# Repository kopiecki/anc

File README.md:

# Active noise reduction system under the supervision of the Linux kernel with real-time extensions
The repository contains hardware, firmware and system software for master thesis project.

# Project structure
Project consists of a following modules:
- **base** - docker related stuff
- **hardware** - KiCAD electronics and PCB design
- **software** - application software environment
- **system** - system software, GNU/Linux OS building tools
- **docs** - school presentations and thesis draft

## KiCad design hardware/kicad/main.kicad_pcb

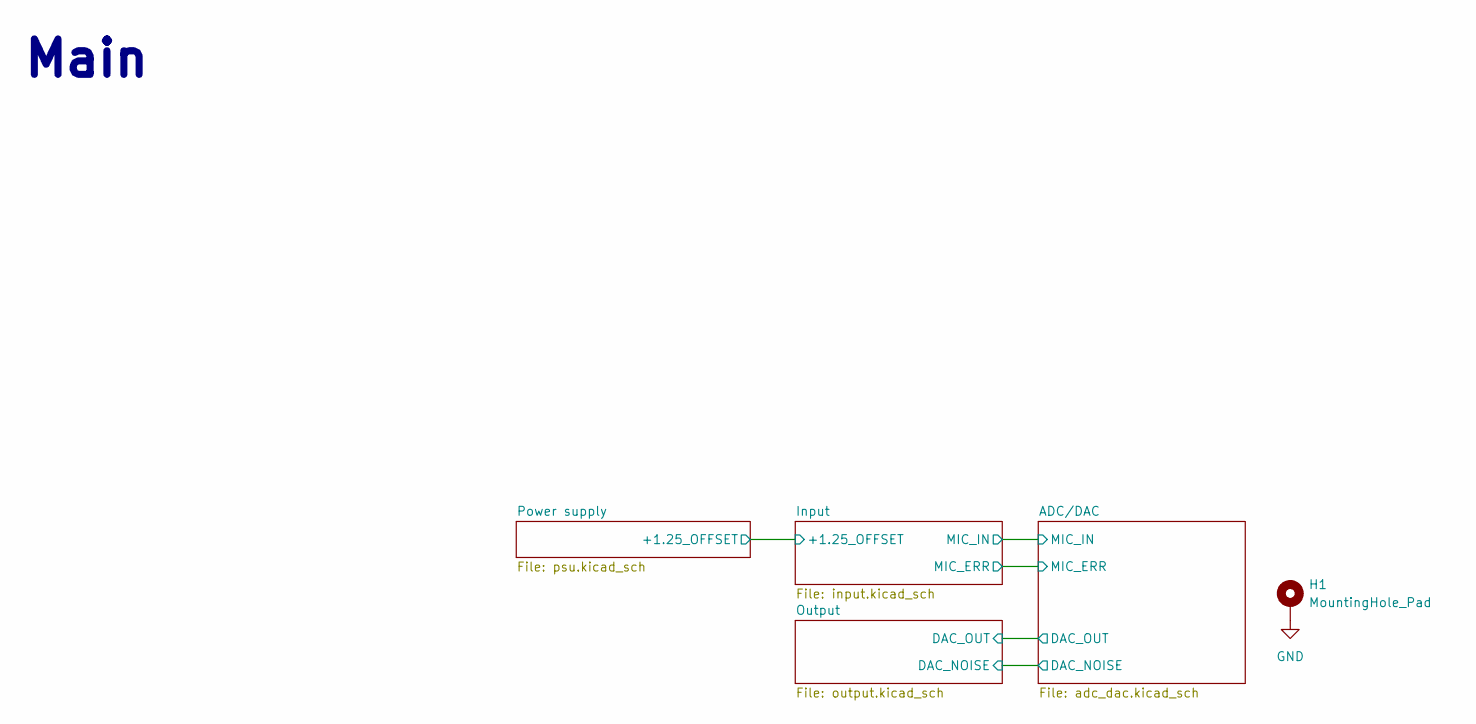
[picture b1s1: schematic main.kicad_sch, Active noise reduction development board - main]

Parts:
H1: MountingHole_Pad; MountingHole_2.7mm_Pad

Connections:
GND: H1.1; also elsewhere on the board

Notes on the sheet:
Main

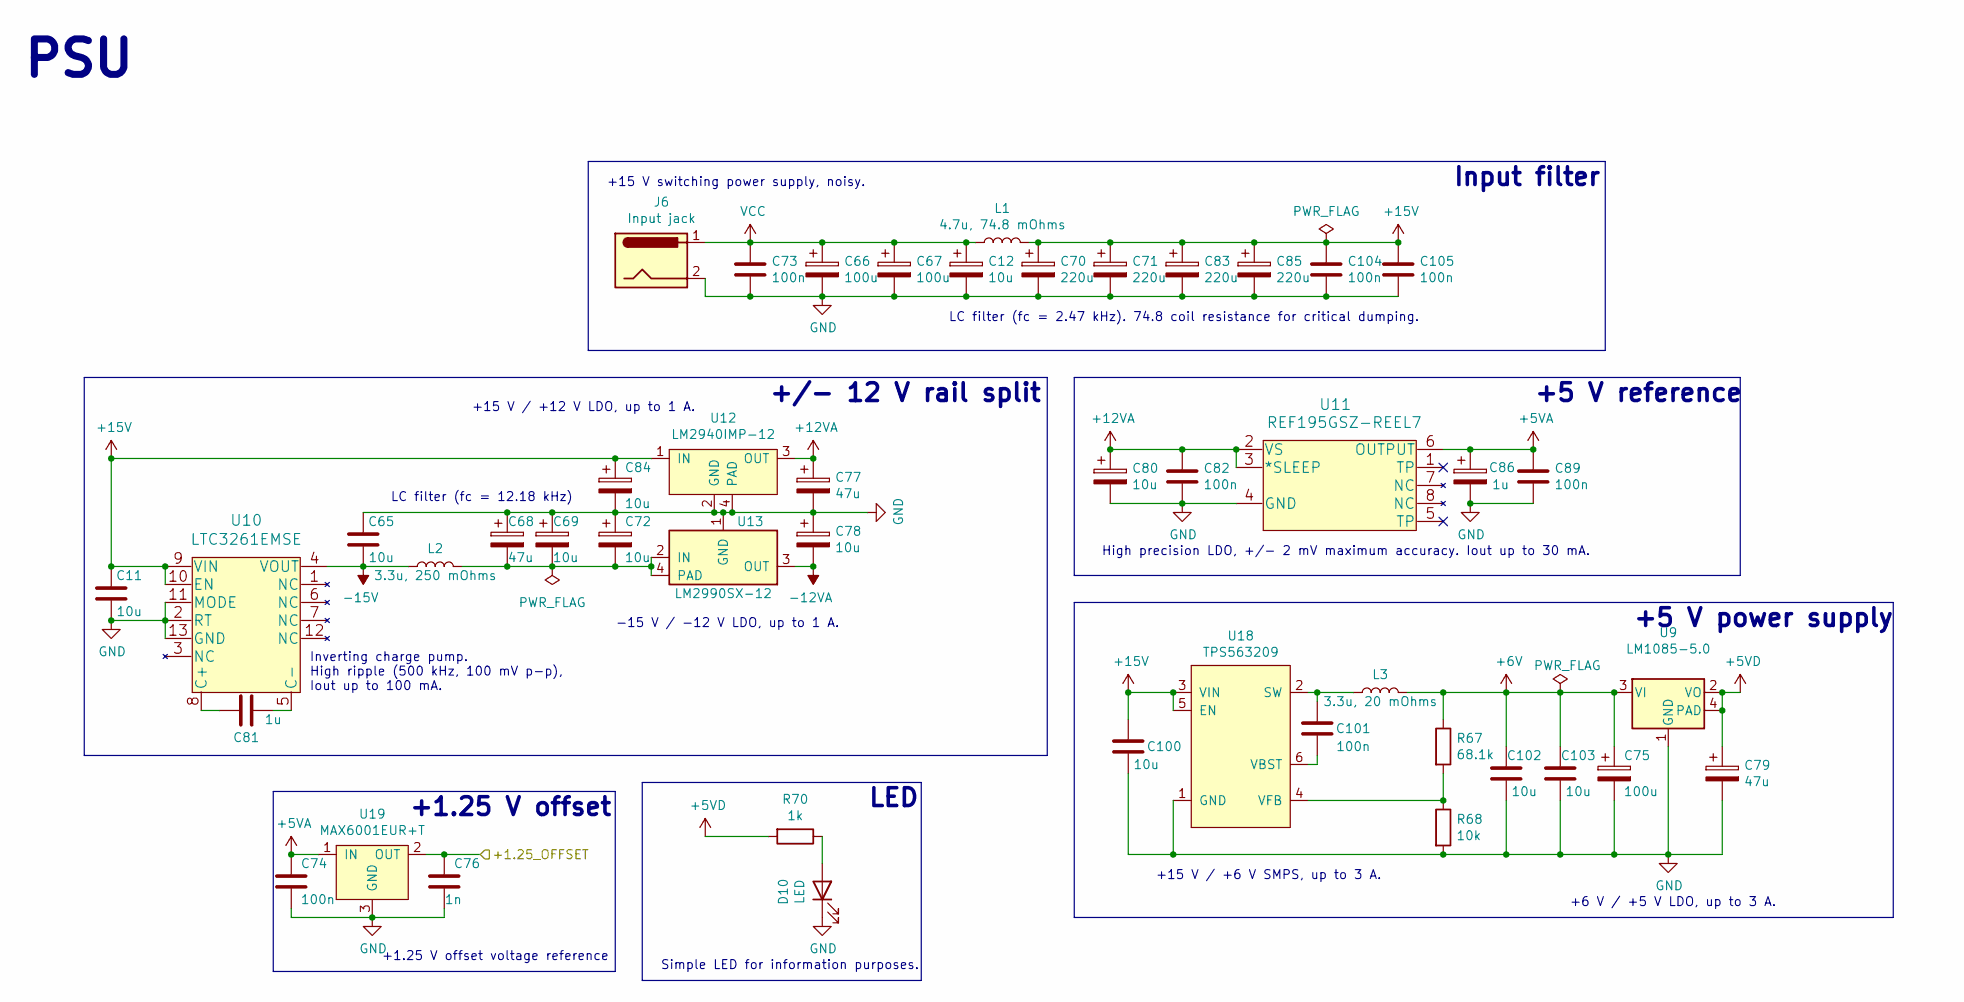
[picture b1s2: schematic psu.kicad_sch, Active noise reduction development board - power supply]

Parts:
C11, C65, C100, C102, C103: 10u; C_0805_2012Metric
C12, C69, C72, C78, C80, C84: 10u; CP_Elec_6.3x5.8
C66, C67, C75: 100u; CP_Elec_6.3x7.7
C68, C77, C79: 47u; CP_Elec_6.3x7.7
C70, C71, C83, C85: 220u; CP_Elec_10x10
C73, C74, C82, C89, C101, C104, C105: 100n; C_0603_1608Metric
C76: 1n; C_0603_1608Metric
C81: 1u; C_0603_1608Metric
C86: 1u; CP_Elec_4x5.4
D10: LED; LED_0603_1608Metric
J6: Input jack; BarrelJack_Horizontal
L1: 4.7u, 74.8 mOhms; L_Wuerth_MAPI-4020
L2: 3.3u, 250 mOhms; L_0805_2012Metric
L3: 3.3u, 20 mOhms; L_Wuerth_WE-PD2-Typ-L
R67: 68.1k; R_0805_2012Metric
R68: 10k; R_0805_2012Metric
R70: 1k; R_0603_1608Metric
U9: LM1085-5.0; LM1085IS-12&slash_NOPB
U10: LTC3261EMSE; ltc3261emse-pbf
U11: REF195GSZ-REEL7
U12: LM2940IMP-12; LM2940IMP-10&slash_NOPB
U13: LM2990SX-12; LM2990S-12
U18: TPS563209; TPS563209DDCR
U19: MAX6001EUR+T; SOT-23

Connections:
+5VA: C74.1, C86.1, C89.1, U11.6 (OUTPUT), U19.1 (IN); also elsewhere on the board
+5VD: C79.1, R70.2, U9.2 (VO), U9.4 (PAD); also elsewhere on the board
+6V: C75.1, C102.2, C103.2, L3.2, R67.1, U9.3 (VI)
+12VA: C77.1, C80.1, C82.1, U11.2 (VS), U11.3 (*SLEEP), U12.3 (OUT); also elsewhere on the board
+15V: C11.2, C70.1, C71.1, C83.1, C84.1, C85.1, C100.2, C104.1, C105.1, L1.2, U10.9 (VIN), U10.10 (EN), U12.1 (IN), U18.3 (VIN), U18.5 (EN)
-12VA: C78.2, U13.3 (OUT); also elsewhere on the board
-15V: C65.1, L2.1, U10.4 (VOUT)
/Input/+1.25_OFFSET: C76.1, U19.2 (OUT); also elsewhere on the board
GND: C11.1, C12.2, C65.2, C66.2, C67.2, C68.1, C69.1, C70.2, C71.2, C72.1, C73.2, C74.2, C75.2, C76.2, C77.2, C78.1, C79.2, C80.2, C82.2, C83.2, C84.2, C85.2, C86.2, C89.2, C100.1, C102.1, C103.1, C104.2, C105.2, D10.1 (K), J6.2, R68.2, U9.1 (GND), U10.2 (RT), U10.11 (MODE), U10.13 (GND), U11.4 (GND), U12.2 (GND), U12.4 (PAD), U13.1 (GND), U18.1 (GND), U19.3 (GND); also elsewhere on the board
unnamed: C68.2, C69.2, C72.2, L2.2, U13.2 (IN), U13.4 (PAD)
unnamed: C81.1, U10.8 (C+)
unnamed: C81.2, U10.5 (C-)
unnamed: C101.1, U18.6 (VBST)
unnamed: C101.2, L3.1, U18.2 (SW)
unnamed: D10.2 (A), R70.1
unnamed: R67.2, R68.1, U18.4 (VFB)
VCC: C12.1, C66.1, C67.1, C73.1, J6.1, L1.1

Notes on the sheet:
+15 V switching power supply, noisy.
LC filter (fc = 12.18 kHz)
PSU
LED
+15 V / +12 V LDO, up to 1 A.
Simple LED for information purposes.
-15 V / -12 V LDO, up to 1 A.
Inverting charge pump. High ripple (500 kHz, 100 mV p-p), Iout up to 100 mA.
Input filter
LC filter (fc = 2.47 kHz). 74.8 coil resistance for critical dumping.
+5 V power supply
+5 V reference
+6 V / +5 V LDO, up to 3 A.
+/- 12 V rail split
+15 V / +6 V SMPS, up to 3 A.
+1.25 V offset voltage reference
High precision LDO, +/- 2 mV maximum accuracy. Iout up to 30 mA.
+1.25 V offset

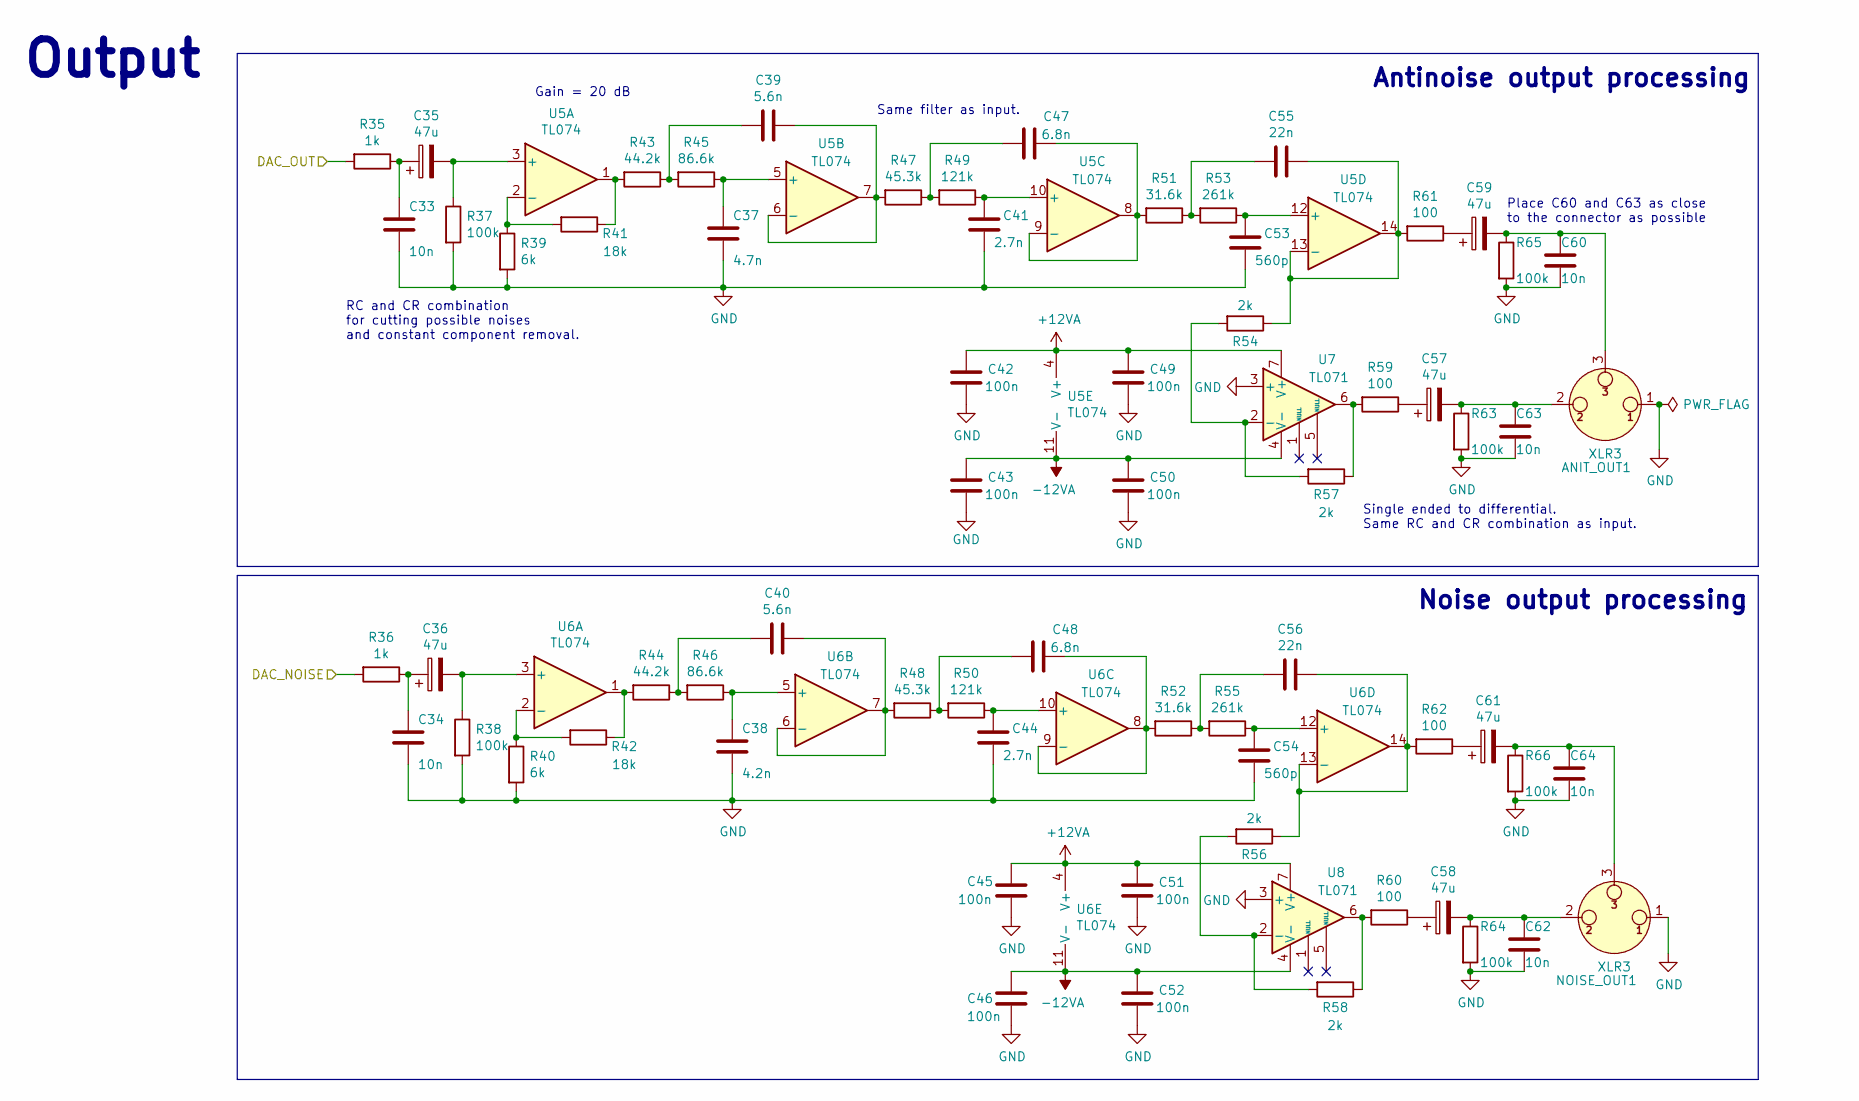
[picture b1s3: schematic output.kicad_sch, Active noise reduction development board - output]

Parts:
ANIT_OUT1: XLR3; Jack_XLR_Neutrik_NC3MAH-0_Horizontal
C33, C34, C60, C62, C63, C64: 10n; C_0603_1608Metric
C35, C36, C57, C58, C59, C61: 47u; CP_Elec_6.3x7.7
C37: 4.7n; C_0603_1608Metric
C38: 4.2n; C_0603_1608Metric
C39, C40: 5.6n; C_0603_1608Metric
C41, C44: 2.7n; C_0603_1608Metric
C42, C43, C45, C46, C49, C50, C51, C52: 100n; C_0603_1608Metric
C47, C48: 6.8n; C_0603_1608Metric
C53, C54: 560p; C_0603_1608Metric
C55, C56: 22n; C_0603_1608Metric
NOISE_OUT1: XLR3; Jack_XLR_Neutrik_NC3MAH-0_Horizontal
R35, R36: 1k; R_0603_1608Metric
R37, R38, R63, R64, R65, R66: 100k; R_0603_1608Metric
R39, R40: 6k; R_0603_1608Metric
R41, R42: 18k; R_0603_1608Metric
R43, R44: 44.2k; R_0603_1608Metric
R45, R46: 86.6k; R_0603_1608Metric
R47, R48: 45.3k; R_0603_1608Metric
R49, R50: 121k; R_0603_1608Metric
R51, R52: 31.6k; R_0603_1608Metric
R53, R55: 261k; R_0603_1608Metric
R54, R56, R57, R58: 2k; R_0603_1608Metric
R59, R60, R61, R62: 100; R_0603_1608Metric
U5, U6: TL074; TL074CD
U7, U8: TL071; TL071CD

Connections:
+12VA: C42.1, C45.1, C49.1, C51.1, U5.4 (V+), U6.4 (V+), U7.7 (V+), U8.7 (V+); also elsewhere on the board
-12VA: C43.1, C46.1, C50.1, C52.1, U5.11 (V-), U6.11 (V-), U7.4 (V-), U8.4 (V-); also elsewhere on the board
/ADC/DAC/DAC_NOISE: R36.2; also elsewhere on the board
/ADC/DAC/DAC_OUT: R35.2; also elsewhere on the board
GND: ANIT_OUT1.1, C33.2, C34.2, C37.2, C38.2, C41.2, C42.2, C43.2, C44.2, C45.2, C46.2, C49.2, C50.2, C51.2, C52.2, C53.2, C54.2, C60.2, C62.2, C63.2, C64.2, NOISE_OUT1.1, R37.2, R38.2, R39.2, R40.2, R63.2, R64.2, R65.2, R66.2, U7.3 (+), U8.3 (+); also elsewhere on the board
unnamed: ANIT_OUT1.2, C57.2, C63.1, R63.1
unnamed: ANIT_OUT1.3, C59.2, C60.1, R65.1
unnamed: C33.1, C35.1, R35.1
unnamed: C34.1, C36.1, R36.1
unnamed: C35.2, R37.1, U5.3 (+)
unnamed: C36.2, R38.1, U6.3 (+)
unnamed: C37.1, R45.1, U5.5 (+)
unnamed: C38.1, R46.1, U6.5 (+)
unnamed: C39.1, R43.1, R45.2
unnamed: C39.2, R47.2, U5.6 (-), U5.7
unnamed: C40.1, R44.1, R46.2
unnamed: C40.2, R48.2, U6.6 (-), U6.7
unnamed: C41.1, R49.1, U5.10 (+)
unnamed: C44.1, R50.1, U6.10 (+)
unnamed: C47.1, R47.1, R49.2
unnamed: C47.2, R51.2, U5.8, U5.9 (-)
unnamed: C48.1, R48.1, R50.2
unnamed: C48.2, R52.2, U6.8, U6.9 (-)
unnamed: C53.1, R53.1, U5.12 (+)
unnamed: C54.1, R55.1, U6.12 (+)
unnamed: C55.1, R51.1, R53.2
unnamed: C55.2, R54.1, R61.2, U5.13 (-), U5.14
unnamed: C56.1, R52.1, R55.2
unnamed: C56.2, R56.1, R62.2, U6.13 (-), U6.14
unnamed: C57.1, R59.1
unnamed: C58.1, R60.1
unnamed: C58.2, C62.1, NOISE_OUT1.2, R64.1
unnamed: C59.1, R61.1
unnamed: C61.1, R62.1
unnamed: C61.2, C64.1, NOISE_OUT1.3, R66.1
unnamed: R39.1, R41.2, U5.2 (-)
unnamed: R40.1, R42.2, U6.2 (-)
unnamed: R41.1, R43.2, U5.1
unnamed: R42.1, R44.2, U6.1
unnamed: R54.2, R57.2, U7.2 (-)
unnamed: R56.2, R58.2, U8.2 (-)
unnamed: R57.1, R59.2, U7.6
unnamed: R58.1, R60.2, U8.6

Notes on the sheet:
Place C60 and C63 as close to the connector as possible
Output
Gain = 20 dB
RC and CR combination for cutting possible noises and constant component removal.
Single ended to differential. Same RC and CR combination as input.
Noise output processing
Same filter as input.
Antinoise output processing

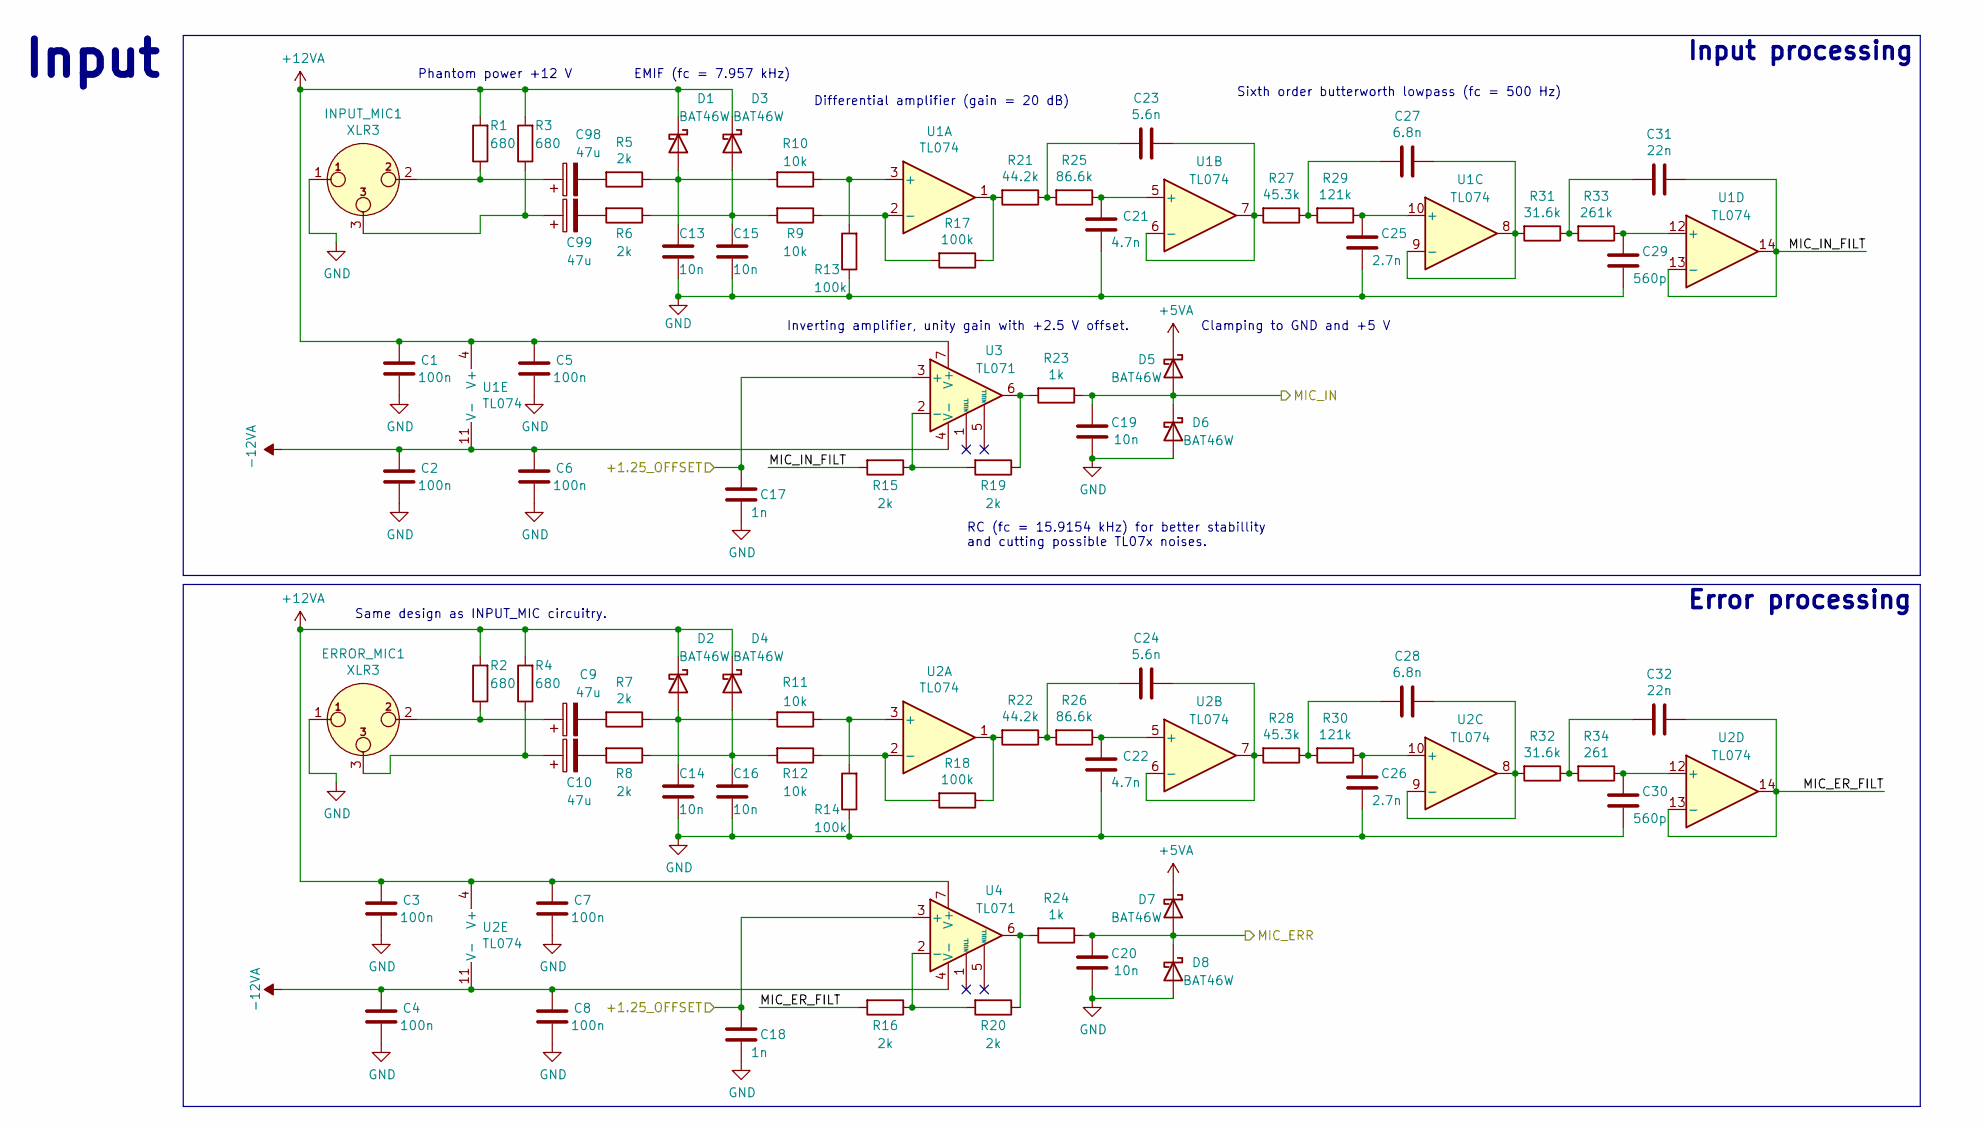
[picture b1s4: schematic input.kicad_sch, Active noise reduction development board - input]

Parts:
C1, C2, C3, C4, C5, C6, C7, C8: 100n; C_0603_1608Metric
C9, C10, C98, C99: 47u; CP_Elec_6.3x7.7
C13, C14, C15, C16, C19, C20: 10n; C_0603_1608Metric
C17, C18: 1n; C_0603_1608Metric
C21, C22: 4.7n; C_0603_1608Metric
C23, C24: 5.6n; C_0603_1608Metric
C25, C26: 2.7n; C_0603_1608Metric
C27, C28: 6.8n; C_0603_1608Metric
C29, C30: 560p; C_0603_1608Metric
C31, C32: 22n; C_0603_1608Metric
D1, D2, D3, D4, D5, D6, D7, D8: BAT46W; D_SOD-123F
ERROR_MIC1: XLR3; Jack_XLR_Neutrik_NC3MAH-0_Horizontal
INPUT_MIC1: XLR3; Jack_XLR_Neutrik_NC3MAH-0_Horizontal
R1, R2, R3, R4: 680; R_0805_2012Metric
R5, R6, R7, R8, R15, R16, R19, R20: 2k; R_0603_1608Metric
R9, R10, R11, R12: 10k; R_0603_1608Metric
R13, R14, R17, R18: 100k; R_0603_1608Metric
R21, R22: 44.2k; R_0603_1608Metric
R23, R24: 1k; R_0603_1608Metric
R25, R26: 86.6k; R_0603_1608Metric
R27, R28: 45.3k; R_0603_1608Metric
R29, R30: 121k; R_0603_1608Metric
R31, R32: 31.6k; R_0603_1608Metric
R33: 261k; R_0603_1608Metric
R34: 261; R_0603_1608Metric
U1, U2: TL074; TL074CD
U3, U4: TL071; TL071CD

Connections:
+5VA: D5.1 (K), D7.1 (K); also elsewhere on the board
+12VA: C1.1, C3.1, C5.1, C7.1, D1.1 (K), D2.1 (K), D3.1 (K), D4.1 (K), R1.2, R2.2, R3.2, R4.2, U1.4 (V+), U2.4 (V+), U3.7 (V+), U4.7 (V+); also elsewhere on the board
-12VA: C2.1, C4.1, C6.1, C8.1, U1.11 (V-), U2.11 (V-), U3.4 (V-), U4.4 (V-); also elsewhere on the board
/ADC/DAC/MIC_ERR: C20.1, D7.2 (A), D8.1 (K), R24.1; also elsewhere on the board
/ADC/DAC/MIC_IN: C19.1, D5.2 (A), D6.1 (K), R23.1; also elsewhere on the board
/Input/+1.25_OFFSET: C17.1, C18.1, U3.3 (+), U4.3 (+); also elsewhere on the board
/Input/MIC_ER_FILT: C32.2, R16.2, U2.13 (-), U2.14
/Input/MIC_IN_FILT: C31.2, R15.2, U1.13 (-), U1.14
GND: C1.2, C2.2, C3.2, C4.2, C5.2, C6.2, C7.2, C8.2, C13.2, C14.2, C15.2, C16.2, C17.2, C18.2, C19.2, C20.2, C21.2, C22.2, C25.2, C26.2, C29.2, C30.2, D6.2 (A), D8.2 (A), ERROR_MIC1.1, INPUT_MIC1.1, R13.1, R14.1; also elsewhere on the board
unnamed: C9.1, ERROR_MIC1.2, R2.1
unnamed: C9.2, R7.2
unnamed: C10.1, ERROR_MIC1.3, R4.1
unnamed: C10.2, R8.2
unnamed: C13.1, D1.2 (A), R5.1, R10.2
unnamed: C14.1, D2.2 (A), R7.1, R11.2
unnamed: C15.1, D3.2 (A), R6.1, R9.2
unnamed: C16.1, D4.2 (A), R8.1, R12.2
unnamed: C21.1, R25.1, U1.5 (+)
unnamed: C22.1, R26.1, U2.5 (+)
unnamed: C23.1, R21.1, R25.2
unnamed: C23.2, R27.2, U1.6 (-), U1.7
unnamed: C24.1, R22.1, R26.2
unnamed: C24.2, R28.2, U2.6 (-), U2.7
unnamed: C25.1, R29.1, U1.10 (+)
unnamed: C26.1, R30.1, U2.10 (+)
unnamed: C27.1, R27.1, R29.2
unnamed: C27.2, R31.2, U1.8, U1.9 (-)
unnamed: C28.1, R28.1, R30.2
unnamed: C28.2, R32.2, U2.8, U2.9 (-)
unnamed: C29.1, R33.1, U1.12 (+)
unnamed: C30.1, R34.1, U2.12 (+)
unnamed: C31.1, R31.1, R33.2
unnamed: C32.1, R32.1, R34.2
unnamed: C98.1, INPUT_MIC1.2, R1.1
unnamed: C98.2, R5.2
unnamed: C99.1, INPUT_MIC1.3, R3.1
unnamed: C99.2, R6.2
unnamed: R10.1, R13.2, U1.3 (+)
unnamed: R11.1, R14.2, U2.3 (+)
unnamed: R12.1, R18.2, U2.2 (-)
unnamed: R15.1, R19.2, U3.2 (-)
unnamed: R16.1, R20.2, U4.2 (-)
unnamed: R17.1, R21.2, U1.1
unnamed: R9.1, R17.2, U1.2 (-)
unnamed: R18.1, R22.2, U2.1
unnamed: R19.1, R23.2, U3.6
unnamed: R20.1, R24.2, U4.6

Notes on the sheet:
Phantom power +12 V
Same design as INPUT_MIC circuitry.
Differential amplifier (gain = 20 dB)
Sixth order butterworth lowpass (fc = 500 Hz)
RC (fc = 15.9154 kHz) for better stabillity and cutting possible TL07x noises.
Clamping to GND and +5 V
Error processing
Input
Inverting amplifier, unity gain with +2.5 V offset.
Input processing
EMIF (fc = 7.957 kHz)

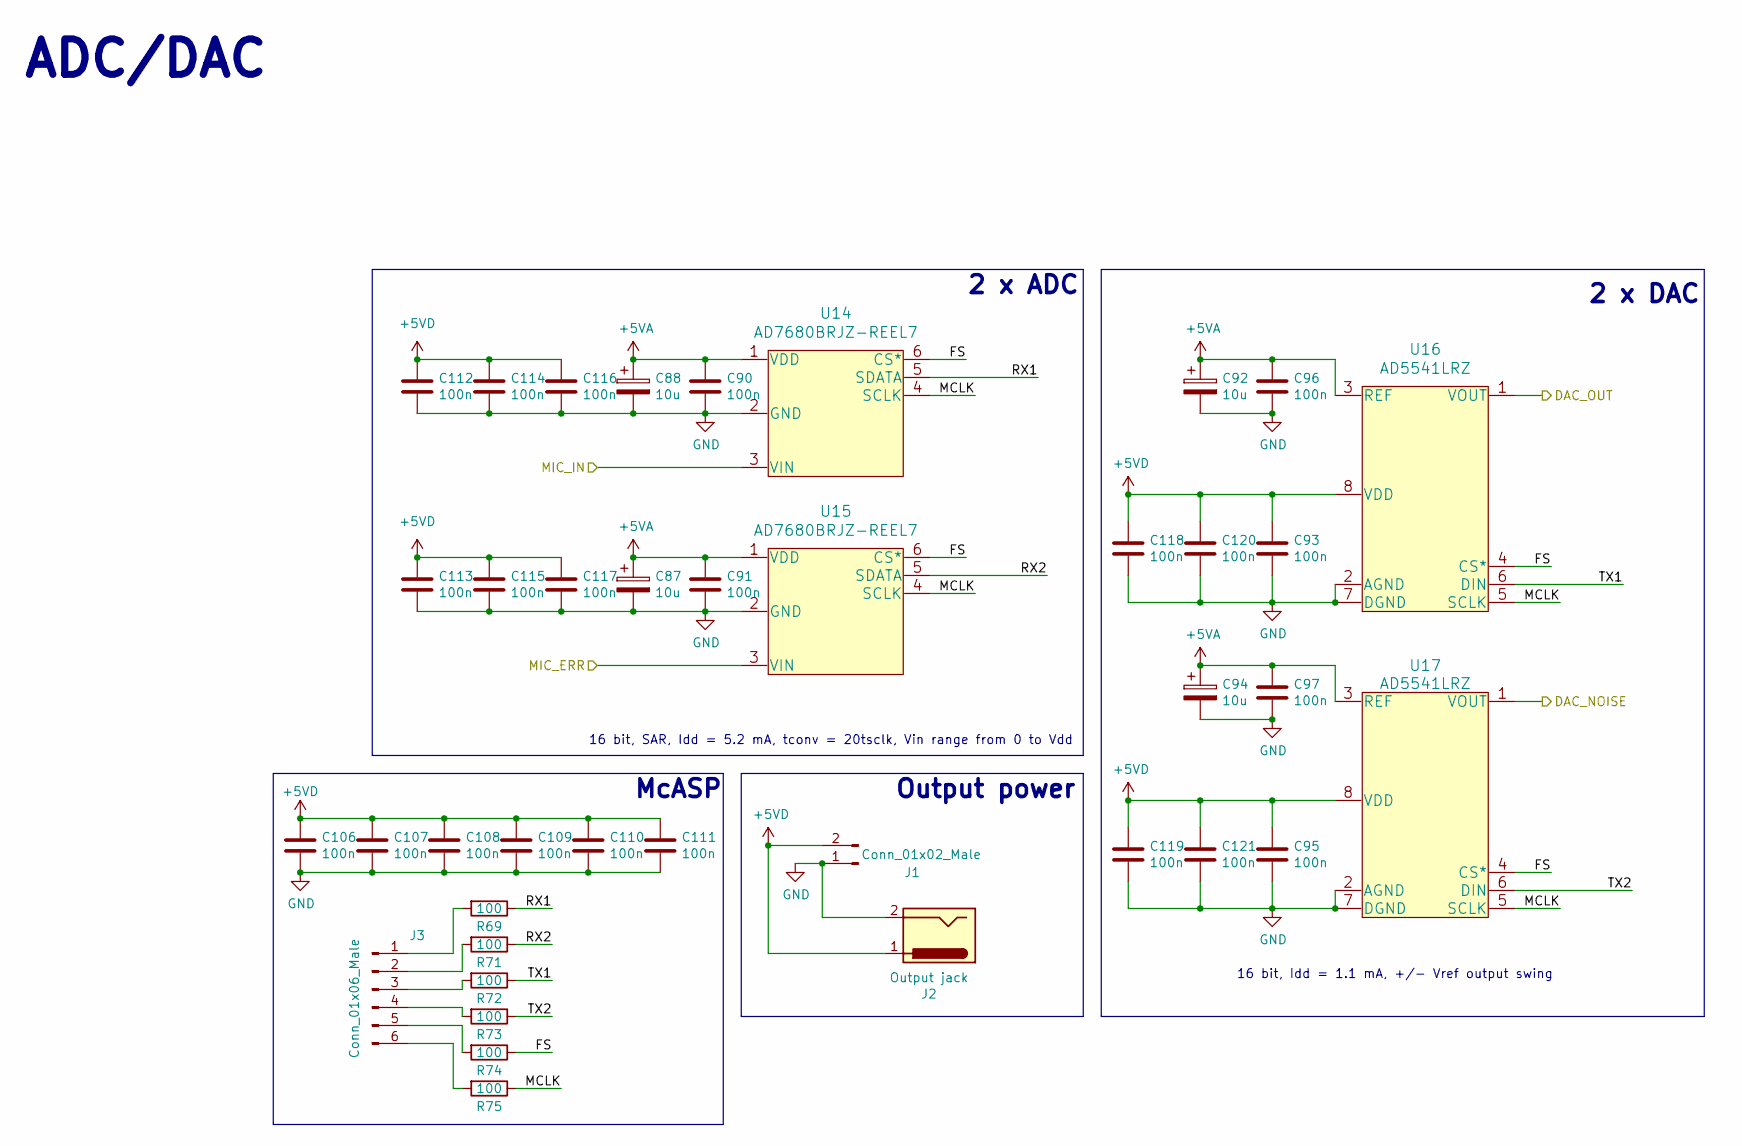
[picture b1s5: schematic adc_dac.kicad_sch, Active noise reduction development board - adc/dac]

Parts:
C87, C88, C92, C94: 10u; CP_Elec_6.3x5.8
C90, C91, C93, C95, C96, C97, C106, C107, C108, C109, C110, C111, C112, C113, C114, C115, C116, C117, C118, C119, C120, C121: 100n; C_0603_1608Metric
J1: Conn_01x02_Male; PinHeader_1x02_P2.54mm_Vertical
J2: Output jack; BarrelJack_Horizontal
J3: Conn_01x06_Male; PinHeader_1x06_P2.54mm_Vertical
R69, R71, R72, R73, R74, R75: 100; R_0603_1608Metric
U14, U15: AD7680BRJZ-REEL7
U16, U17: AD5541LRZ

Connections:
+5VA: C87.1, C88.1, C90.1, C91.1, C92.1, C94.1, C96.1, C97.1, U14.1 (VDD), U15.1 (VDD), U16.3 (REF), U17.3 (REF); also elsewhere on the board
+5VD: C93.1, C95.1, C106.1, C107.1, C108.1, C109.1, C110.1, C111.1, C112.1, C113.1, C114.1, C115.1, C116.1, C117.1, C118.1, C119.1, C120.1, C121.1, J1.2, J2.1, U16.8 (VDD), U17.8 (VDD); also elsewhere on the board
/ADC/DAC/DAC_NOISE: U17.1 (VOUT); also elsewhere on the board
/ADC/DAC/DAC_OUT: U16.1 (VOUT); also elsewhere on the board
/ADC/DAC/FS: R74.1, U14.6 (CS*), U15.6 (CS*), U16.4 (CS*), U17.4 (CS*)
/ADC/DAC/MCLK: R75.1, U14.4 (SCLK), U15.4 (SCLK), U16.5 (SCLK), U17.5 (SCLK)
/ADC/DAC/MIC_ERR: U15.3 (VIN); also elsewhere on the board
/ADC/DAC/MIC_IN: U14.3 (VIN); also elsewhere on the board
/ADC/DAC/RX1: R69.1, U14.5 (SDATA)
/ADC/DAC/RX2: R71.1, U15.5 (SDATA)
/ADC/DAC/TX1: R72.1, U16.6 (DIN)
/ADC/DAC/TX2: R73.1, U17.6 (DIN)
GND: C87.2, C88.2, C90.2, C91.2, C92.2, C93.2, C94.2, C95.2, C96.2, C97.2, C106.2, C107.2, C108.2, C109.2, C110.2, C111.2, C112.2, C113.2, C114.2, C115.2, C116.2, C117.2, C118.2, C119.2, C120.2, C121.2, J1.1, J2.2, U14.2 (GND), U15.2 (GND), U16.2 (AGND), U16.7 (DGND), U17.2 (AGND), U17.7 (DGND); also elsewhere on the board
unnamed: J3.1, R69.2
unnamed: J3.2, R71.2
unnamed: J3.3, R72.2
unnamed: J3.4, R73.2
unnamed: J3.5, R74.2
unnamed: J3.6, R75.2

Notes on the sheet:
2 x ADC
16 bit, Idd = 1.1 mA, +/- Vref output swing
2 x DAC
16 bit, SAR, Idd = 5.2 mA, tconv = 20tsclk, Vin range from 0 to Vdd
McASP
ADC/DAC
Output power

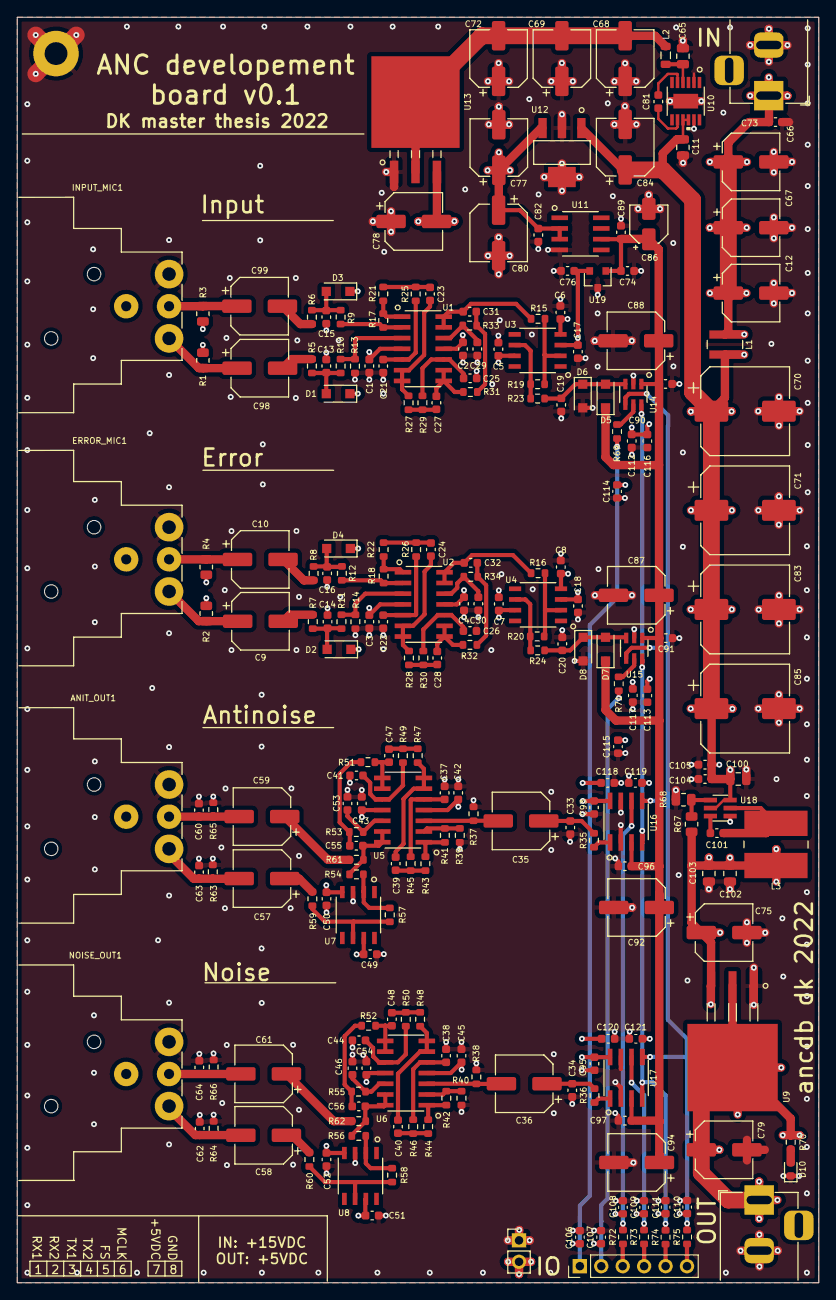
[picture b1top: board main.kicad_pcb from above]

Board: 4 copper layers, 95.0 x 150.0 mm, 236 parts (0 on the bottom side), 111 nets.

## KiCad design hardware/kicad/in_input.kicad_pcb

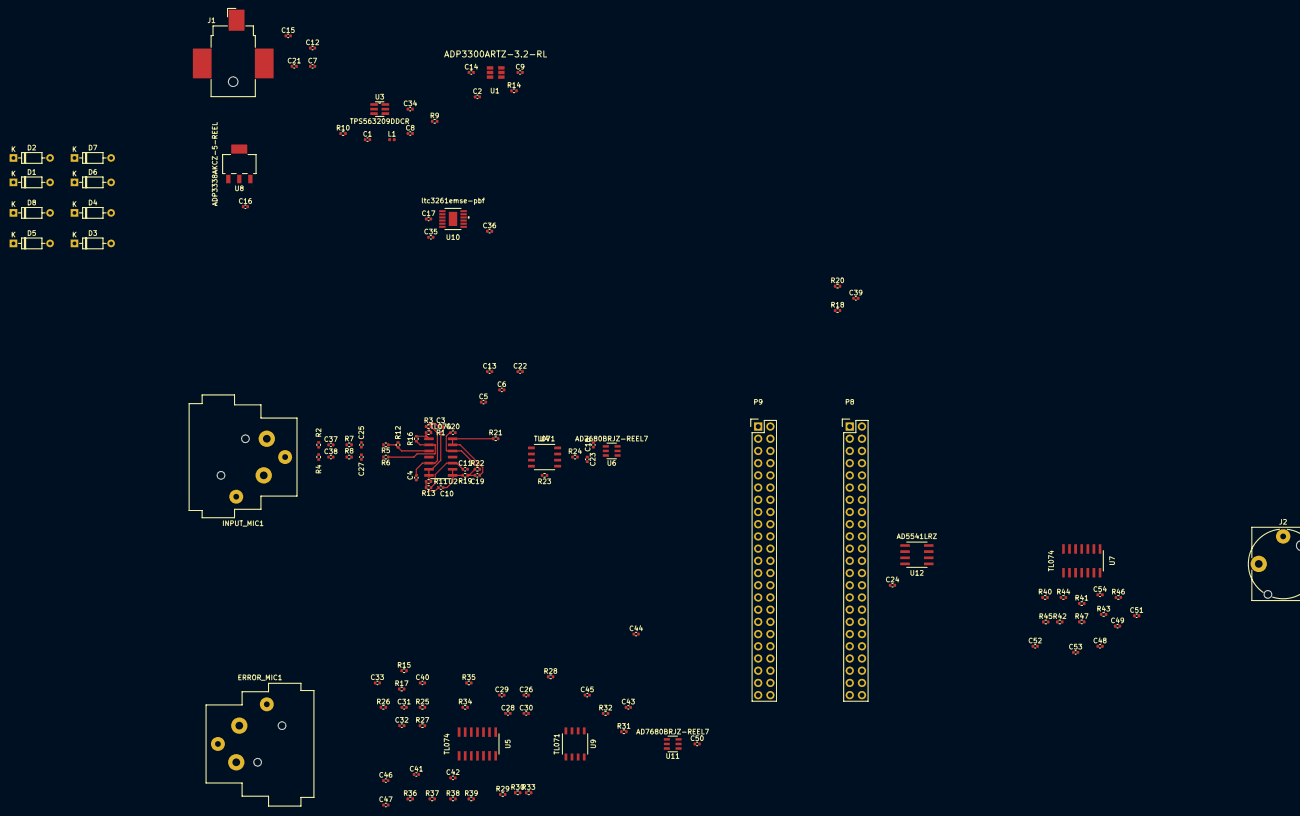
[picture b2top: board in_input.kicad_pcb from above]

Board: 2 copper layers, 128 parts (0 on the bottom side), 72 nets.

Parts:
C1, C15, C18, C21, C24, C35, C36, C39, C50: 10u; C_0402_1005Metric
C2, C9: 0.47u; C_0402_1005Metric
C3, C43, C49: 2.5n; C_0402_1005Metric
C4, C42, C48: 2n; C_0402_1005Metric
C5, C6, C8, C13, C22, C26, C28, C29, C30: 100n; C_0402_1005Metric
C7, C12: 1m; C_0402_1005Metric
C10, C45, C52: 3.3n; C_0402_1005Metric
C11, C44, C51: 1.3n; C_0402_1005Metric
C14, C16, C17: 1u; C_0402_1005Metric
C19, C47, C54: 9n; C_0402_1005Metric
C20, C46, C53: 44n; C_0402_1005Metric
C23, C41: 27n; C_0402_1005Metric
C25, C27, C33, C40: 1n; C_0402_1005Metric
C31, C32, C34, C37, C38: 22u; C_0402_1005Metric
D1, D2, D3, D4, D5, D6, D7, D8: BAT46W; D_DO-35_SOD27_P7.62mm_Horizontal
ERROR_MIC1: XLR3; Jack_XLR_Neutrik_NC3FAH2_Horizontal
INPUT_MIC1: XLR3; Jack_XLR_Neutrik_NC3FAH2_Horizontal
J1: Jack-DC; BarrelJack_CUI_PJ-036AH-SMT_Horizontal
J2: AudioJack2; Jack_6.35mm_Neutrik_NJ2FD-V_Vertical
L1: 3.3u; L_0402_1005Metric
P8, P9: BeagleBone_Black_Header; Socket_BeagleBone_Black
R1, R11, R19, R34, R36, R38, R42, R44, R46: 47k; R_0402_1005Metric
R2, R4, R5, R6, R7, R8, R15, R17, R21, R23, R25, R26, R27, R28, R29, R30: 1k; R_0402_1005Metric
R3, R35, R43: 100k; R_0402_1005Metric
R9: 82.5k; R_0402_1005Metric
R10, R12, R16, R18, R20, R31, R32: 10k; R_0402_1005Metric
R13, R37, R45: 120k; R_0402_1005Metric
R14: 330k; R_0402_1005Metric
R22, R39, R47: 140k; R_0402_1005Metric
R24, R33: 33; R_0402_1005Metric
R40: 2k; R_0402_1005Metric
R41: 18k; R_0402_1005Metric
U1: ADP3300ARTZ-3.2-RL; Analog_Devices-ADP3300ARTZ-3.2-RL-Level_A
U2, U5, U7: TL074; TL074CD
U3: TPS563209DDCR
U4, U9: TL071; TL071CD
U6, U11: AD7680BRJZ-REEL7
U8: ADP3338AKCZ-5-REEL
U10: ltc3261emse-pbf
U12: AD5541LRZ

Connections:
+15V: C1.1, C5.1, C7.1, C12.1, C13.1, C15.1, C21.1, C26.1, C29.1, C35.1, D1.1, D2.1, D3.1, D5.1, D6.1, D7.1, J1.1, R2.2, R4.2, R15.2, R17.2, U3.3, U3.5, U4.7, U5.4, U7.4, U9.7, U10.9, U10.10
/+2.5_VDC_OFF: C39.1, R18.1, R20.1, U4.3, U9.3
/+5_VDC_REF: C9.1, C18.1, C24.1, C50.1, R14.1, R18.2, U1.4, U6.1, U11.1, U12.3, U12.8
/+5_VDC_SYS: C16.1, U8.2
/-15_VDC_IN: C6.1, C22.1, C28.1, C30.1, C36.1, U4.4, U5.11, U7.11, U9.4, U10.4
/SPI0_CS0: P9.17, U6.6
/SPI0_CS1: P9.19, U11.6
/SPI0_D0: P9.21, U6.5, U11.5
/SPI0_SCLK: P9.22, U6.4, U11.4
/V_DAC: U7.3, U12.1
/V_MIC_ERR: C41.1, R33.1, U11.3
/V_MIC_ERR_FILT: C47.2, R29.2, U5.13, U5.14
/V_MIC_IN: C23.1, R24.1, U6.3
/V_MIC_IN_FILT: C19.2, R21.2, U2.13, U2.14
GND: C1.2, C2.2, C4.2, C5.2, C6.2, C7.2, C9.2, C11.2, C12.2, C13.2, C14.2, C15.2, C16.2, C18.2, C20.2, C21.2, C22.2, C23.2, C24.2, C25.2, C26.2, C27.2, C28.2, C29.2, C30.2, C33.2, C34.2, C35.2, C36.2, C39.2, C40.2, C41.2, C42.2, C44.2, C46.2, C48.2, C50.2, C51.2, C53.2, D4.2, D8.2, ERROR_MIC1.1, INPUT_MIC1.1, J1.2, J2.S, P9.43, P9.44, P9.45, P9.46, R10.2, R12.1, R20.2, R31.1, R40.2, U1.1, U3.1, U6.2, U8.3, U10.2, U10.11, U11.2, U12.2, U12.7
unnamed: C3.1, R1.1, R3.2
unnamed: C3.2, R11.2, U2.6, U2.7
unnamed: C4.1, R3.1, U2.5
unnamed: C8.1, L1.1, U3.2
unnamed: C8.2, U3.6
unnamed: C10.1, R11.1, R13.2
unnamed: C10.2, R19.2, U2.8, U2.9
unnamed: C11.1, R13.1, U2.10
unnamed: C2.1, C14.1, C34.1, L1.2, R9.1, U1.3, U1.5, U8.1
unnamed: C17.1, U10.5
unnamed: C17.2, U10.8
unnamed: C19.1, R19.1, R22.2
unnamed: C20.1, R22.1, U2.12
unnamed: C25.1, R5.2, R7.1
unnamed: C27.1, R6.2, R8.1
unnamed: C31.1, ERROR_MIC1.2, R15.1
unnamed: C31.2, R25.2
unnamed: C32.1, ERROR_MIC1.3, R17.1
unnamed: C32.2, R26.2
unnamed: C33.1, R25.1, R27.2
unnamed: C37.1, INPUT_MIC1.2, R2.1
unnamed: C37.2, R7.2
unnamed: C38.1, INPUT_MIC1.3, R4.1
unnamed: C38.2, R8.2
unnamed: C40.1, R26.1, R28.2
unnamed: C42.1, R35.1, U5.5
unnamed: C43.1, R34.1, R35.2
unnamed: C43.2, R36.2, U5.6, U5.7
unnamed: C44.1, R37.1, U5.10
unnamed: C45.1, R36.1, R37.2
unnamed: C45.2, R38.2, U5.8, U5.9
unnamed: C46.1, R39.1, U5.12
unnamed: C47.1, R38.1, R39.2
unnamed: C48.1, R43.1, U7.5
unnamed: C49.1, R42.1, R43.2
unnamed: C49.2, R44.2, U7.6, U7.7
unnamed: C51.1, R45.1, U7.10
unnamed: C52.1, R44.1, R45.2
unnamed: C52.2, R46.2, U7.8, U7.9
unnamed: C53.1, R47.1, U7.12
unnamed: C54.1, R46.1, R47.2
unnamed: C54.2, J2.T, U7.13, U7.14
unnamed: D1.2, R5.1, R12.2, U2.3
unnamed: D2.2, R6.1, R16.2, U2.2
unnamed: D3.2, D4.1, R23.1, R24.2, U4.6
unnamed: D5.2, R27.1, R31.2, U5.3
unnamed: D6.2, R28.1, R32.2, U5.2
unnamed: D7.2, D8.1, R30.1, R33.2, U9.6
unnamed: P8.1, P8.2, P9.1, P9.2
unnamed: R1.2, R16.1, U2.1
unnamed: R9.2, R10.1, U3.4
unnamed: R14.2, U1.6
unnamed: R21.1, R23.2, U4.2
unnamed: R29.1, R30.2, U9.2
unnamed: R32.1, R34.2, U5.1
unnamed: R40.1, R41.2, U7.2
unnamed: R41.1, R42.2, U7.1

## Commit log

2022-10-25 initial
2022-10-27 docs and full schematic
2022-11-01 docker setup
2022-11-03 linux building
2022-11-05 repo rebase
2022-11-05 cleanups
2022-11-09 new hardware
2022-11-09 new schematics
2022-11-12 working system
2022-11-15 schematics redux
2022-11-16 LC filter
2022-11-30 schematics fixes
2022-12-05 after review
2022-12-19 pcb design
2022-12-19 pcb cleanups
2022-12-20 pcb fixes
2022-12-21 pcb work
2022-12-22 PCB: copper mid
2022-12-26 digital power reference
2023-01-03 GND zone fills on bottom and top, terminating resistors for digital signals
2023-01-17 Production
2023-02-03 Save changes
2023-03-18 Basic alsa driver
2023-03-19 Added ALSA sound card driver (WIP)
2023-03-19 Removed malloc wrapper
2023-03-20 First seminaries presentation
2023-03-21 Finished sd1 report
2023-03-26 added signals module, sound_card refactor
2023-03-26 ring_buffer
2023-03-27 Added test and signals fix
2023-03-28 Added circural lifo and couple unit tests
2023-03-29 Added relative paths in project.yml
2023-03-30 Added couple circ_fifo unit tests
2023-04-02 Working loopback!
2023-04-02 Added functional tests
2023-04-03 functional test
2023-04-04 Sound card poll
2023-04-08 Added lms and fxlms simulation
2023-04-09 Added LMS algo and FORMAT define
2023-04-10 test
2023-04-14 corr ident
2023-04-18 saved work from couple of days
2023-04-22 Add: software cross compilation
2023-07-17 work from couple days
2023-07-23 Work from several days, major repository cleanup
2023-07-23 Added thesis template
2023-07-23 Removed unused friend's thesis
2023-07-24 Brutal fight with McASP and AD5541 successfully completed
2023-07-25 Working on thesis document, added couple hardware chapters
2023-07-26 Working 4 channel TX, finished PSU thesis chapter
2023-07-28 Added more hardware thesis chapters
2023-07-30 Finished output analog hardware description
2023-08-01 Added top-level implementation diagram
2023-08-02 Added intro
2023-08-03 Finished intro
2023-08-04 Writing analysis chapter
2023-08-05 Finished analysis chapter
2023-08-06 Finished design assumptions chapter
2023-08-08 McASP description
2023-08-08 Finished protocol chapter
2023-08-09 Added converters description
2023-08-10 Added hardware guidelines, fixed intro typos
2023-08-12 Fixed typos in intro and analysis section
2023-08-13 Finished hw section, working on sw section
2023-08-14 Big software chapter, close to finishing
2023-08-15 Cleanups, andw verification
2023-08-15 Removed KiCAD backup files
2023-08-15 Removed docs build dirs
2023-08-15 Cleaned up docker and cmake scripts
2023-08-15 Removed thesis build artifacts
2023-08-16 Application template
2023-08-17 Working on secondary path identification
2023-08-17 Added rt functions
2023-08-17 Added pthreads support to CMake build system
2023-08-18 Added ANC loop
2023-08-18 Additional CMake flags
2023-08-19 Based on latency test
2023-08-19 Working on latency example
2023-08-20 Going insane 0
2023-08-31 Added hw docs
2023-10-05 Added prng lib
2023-10-06 Added xoroshrio PRNG
2023-10-07 Added NLMS description
2023-10-08 Added user libs subsection
2023-10-09 Added software description and measurements template
2023-10-09 Removed unused files
2023-10-09 Added feedback neutralization chapter
2023-10-12 Added identification results
2023-10-16 Added measurements from couple of days
2023-10-18 Maybe finished
2023-10-22 Removed thesis build
2023-10-23 Applied review patch
2023-10-23 Review changes, stage 1
2023-10-24 Review changes, stage 2
2023-10-25 Review changes, stage 2.5
2023-10-26 Review changes, stage 3
2023-10-26 Couple fixes
2023-10-26 Review changes, stage 3.5
2023-10-28 Review changes, stage 4
2023-10-29 Minor fixes
2023-10-30 Couple review changes
2023-10-30 Math changes
2023-10-31 After personal review
2023-10-31 Preparations
2023-11-01 Final thesis changes
2023-11-01 Final repository cleanups
2023-11-01 Additional docs
2023-11-01 Final cleanups
2023-11-17 Added final presentation
2023-11-17 Added couple lines to final presentation

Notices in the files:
parts and their libraries:
Copyright 2021 Accelerated Designs. All rights reserved.
